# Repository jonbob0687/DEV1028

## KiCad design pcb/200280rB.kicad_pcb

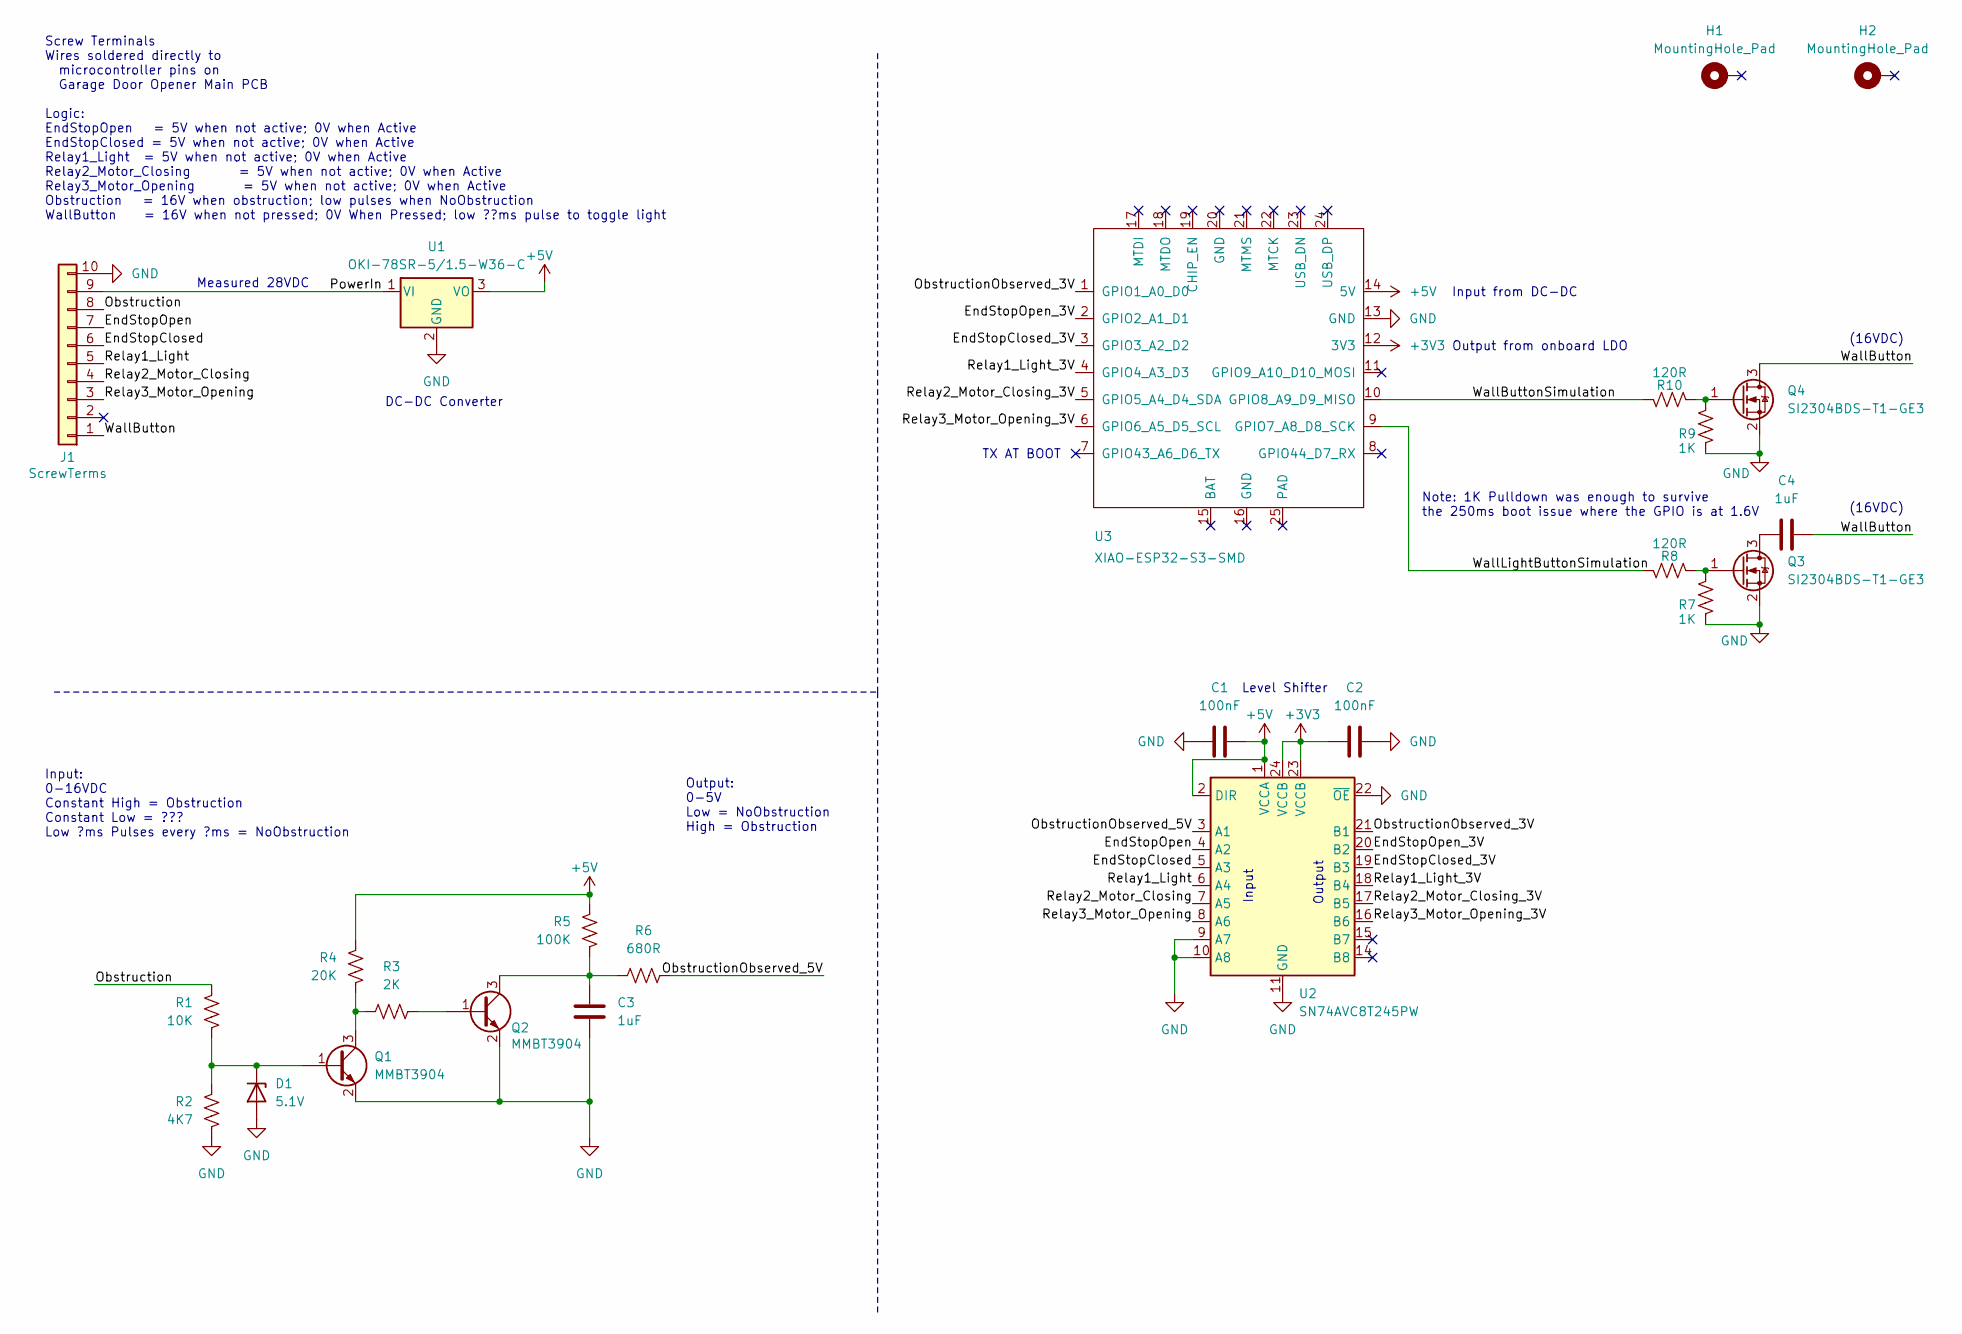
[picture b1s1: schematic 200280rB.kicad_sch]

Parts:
C1, C2: 100nF; C_0603_1608Metric
C3: 1uF; C_0603_1608Metric
C4: 1uF; C_1206_3216Metric_Pad1.33x1.80mm_HandSolder
D1: 5.1V; D_SOD-323_HandSoldering
H1, H2: MountingHole_Pad; MountingHole_3.2mm_M3_Pad
J1: ScrewTerms; phoenix_contact_1984691
Q1, Q2: MMBT3904; SOT-23-3
Q3, Q4: SI2304BDS-T1-GE3; SOT-23
R1: 10K; R_0603_1608Metric
R2: 4K7; R_0603_1608Metric
R3: 2K; R_0603_1608Metric
R4: 20K; R_0603_1608Metric
R5: 100K; R_0603_1608Metric
R6: 680R; R_0603_1608Metric
R7, R9: 1K; R_0603_1608Metric
R8, R10: 120R; R_0603_1608Metric
U1: OKI-78SR-5/1.5-W36-C; TO-220-3_Vertical
U2: SN74AVC8T245PW; TSSOP-24_4.4x7.8mm_P0.65mm
U3: XIAO-ESP32-S3-SMD; XIAO-ESP32S3-SMD

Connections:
+3V3: C2.1, U2.23 (VCCB), U2.24 (VCCB), U3.12 (3V3)
+5V: C1.2, R4.2, R5.2, U1.3 (VO), U2.1 (VCCA), U2.2 (DIR), U3.14 (5V)
/EndStopClosed: J1.6, U2.5 (A3)
/EndStopClosed_3V: U2.19 (B3), U3.3 (GPIO3_A2_D2)
/EndStopOpen: J1.7, U2.4 (A2)
/EndStopOpen_3V: U2.20 (B2), U3.2 (GPIO2_A1_D1)
/Obstruction: J1.8, R1.2
/ObstructionObserved_3V: U2.21 (B1), U3.1 (GPIO1_A0_D0)
/ObstructionObserved_5V: R6.1, U2.3 (A1)
/PowerIn: J1.9, U1.1 (VI)
/Relay1_Light: J1.5, U2.6 (A4)
/Relay1_Light_3V: U2.18 (B4), U3.4 (GPIO4_A3_D3)
/Relay2_Motor_Closing: J1.4, U2.7 (A5)
/Relay2_Motor_Closing_3V: U2.17 (B5), U3.5 (GPIO5_A4_D4_SDA)
/Relay3_Motor_Opening: J1.3, U2.8 (A6)
/Relay3_Motor_Opening_3V: U2.16 (B6), U3.6 (GPIO6_A5_D5_SCL)
/WallButton: C4.2, J1.1, Q4.3 (D)
/WallButtonSimulation: R10.1, U3.10 (GPIO8_A9_D9_MISO)
/WallLightButtonSimulation: R8.1, U3.9 (GPIO7_A8_D8_SCK)
GND: C1.1, C2.2, C3.2, D1.2 (A), J1.10, Q1.2 (E), Q2.2 (E), Q3.2 (S), Q4.2 (S), R2.1, R7.1, R9.1, U1.2 (GND), U2.9 (A7), U2.10 (A8), U2.11 (GND), U2.12 (GND), U2.13 (GND), U2.22 (~OE), U3.13 (GND)
unnamed: D1.1 (K), Q1.1 (B), R1.1, R2.2
unnamed: Q1.3 (C), R3.1, R4.1
unnamed: Q2.1 (B), R3.2
unnamed: C3.1, Q2.3 (C), R5.1, R6.2
unnamed: C4.1, Q3.3 (D)
unnamed: Q3.1 (G), R7.2, R8.2
unnamed: Q4.1 (G), R9.2, R10.2

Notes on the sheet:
(16VDC)
Screw Terminals Wires soldered directly to microcontroller pins on Garage Door Opener Main PCB Logic: EndStopOpen = 5V when not active; 0V when Active EndStopClosed = 5V when not active; 0V when Active Relay1_Light = 5V when not active; 0V when Active Relay2_Motor_Closing = 5V when not active; 0V w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
Output from onboard LDO
Input from DC-DC
Input: 0-16VDC Constant High = Obstruction Constant Low = ??? Low ?ms Pulses every ?ms = NoObstruction
Input
Note: 1K Pulldown was enough to survive the 250ms boot issue where the GPIO is at 1.6V
Output
Measured 28VDC
DC-DC Converter
TX AT BOOT
Level Shifter
Output: 0-5V Low = NoObstruction High = Obstruction

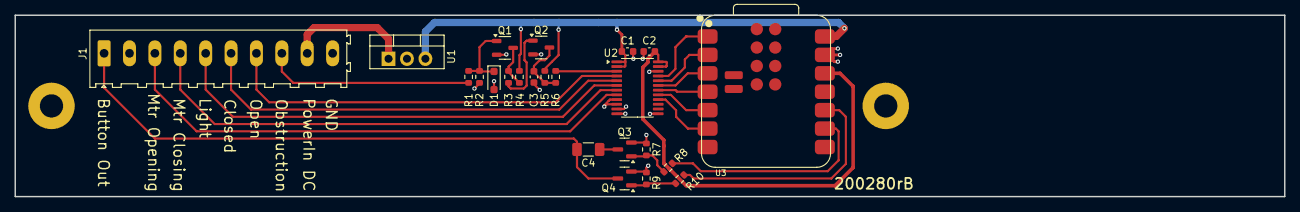
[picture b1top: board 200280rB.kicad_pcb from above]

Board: 2 copper layers, 175.0 x 25.0 mm, 25 parts (0 on the bottom side), 27 nets.

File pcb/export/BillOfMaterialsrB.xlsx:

Reference | Value | Footprint | Qty | DNP | MPN
C1,C2 | 100nF | Capacitor_SMD:C_0603_1608Metric | 2 |  | STASH
C3 | 1uF | Capacitor_SMD:C_0603_1608Metric | 1 |  | CC0603KRX7R9BB105
C4 | 1uF | Capacitor_SMD:C_1206_3216Metric_Pad1.33x1.80mm_HandSolder | 1 |  | HMK316B7105KL-T
D1 | 5.1V | Diode_SMD:D_SOD-323_HandSoldering | 1 |  | DNP
J1 | ScrewTerms | GM_Connector_PhoenixContact:phoenix_contact_1984691 | 1 |  | 1984691
Q1,Q2 | MMBT3904 | Package_TO_SOT_SMD:SOT-23-3 | 2 |  | WORK
Q3,Q4 | SI2304BDS-T1-GE3 | Package_TO_SOT_SMD:SOT-23 | 2 |  | SI2304BDS-T1-GE3
R1 | 10K | Resistor_SMD:R_0603_1608Metric | 1 |  | RC0603FR-0710KL
R2 | 4K7 | Resistor_SMD:R_0603_1608Metric | 1 |  | y
R3 | 2K | Resistor_SMD:R_0603_1608Metric | 1 |  | y
R4 | 20K | Resistor_SMD:R_0603_1608Metric | 1 |  | y
R5 | 100K | Resistor_SMD:R_0603_1608Metric | 1 |  | y
R6 | 680R | Resistor_SMD:R_0603_1608Metric | 1 |  | y
R7,R9 | 1K | Resistor_SMD:R_0603_1608Metric | 2 |  | y
R8,R10 | 120R | Resistor_SMD:R_0603_1608Metric | 2 |  | y
U1 | OKI-78SR-5/1.5-W36-C | Package_TO_SOT_THT:TO-220-3_Vertical | 1 |  | old
U2 | SN74AVC8T245PW | Package_SO:TSSOP-24_4.4x7.8mm_P0.65mm | 1 |  | y
U3 | XIAO-ESP32-S3-SMD | Seeed Studio XIAO Series Library:XIAO-ESP32S3-SMD | 1

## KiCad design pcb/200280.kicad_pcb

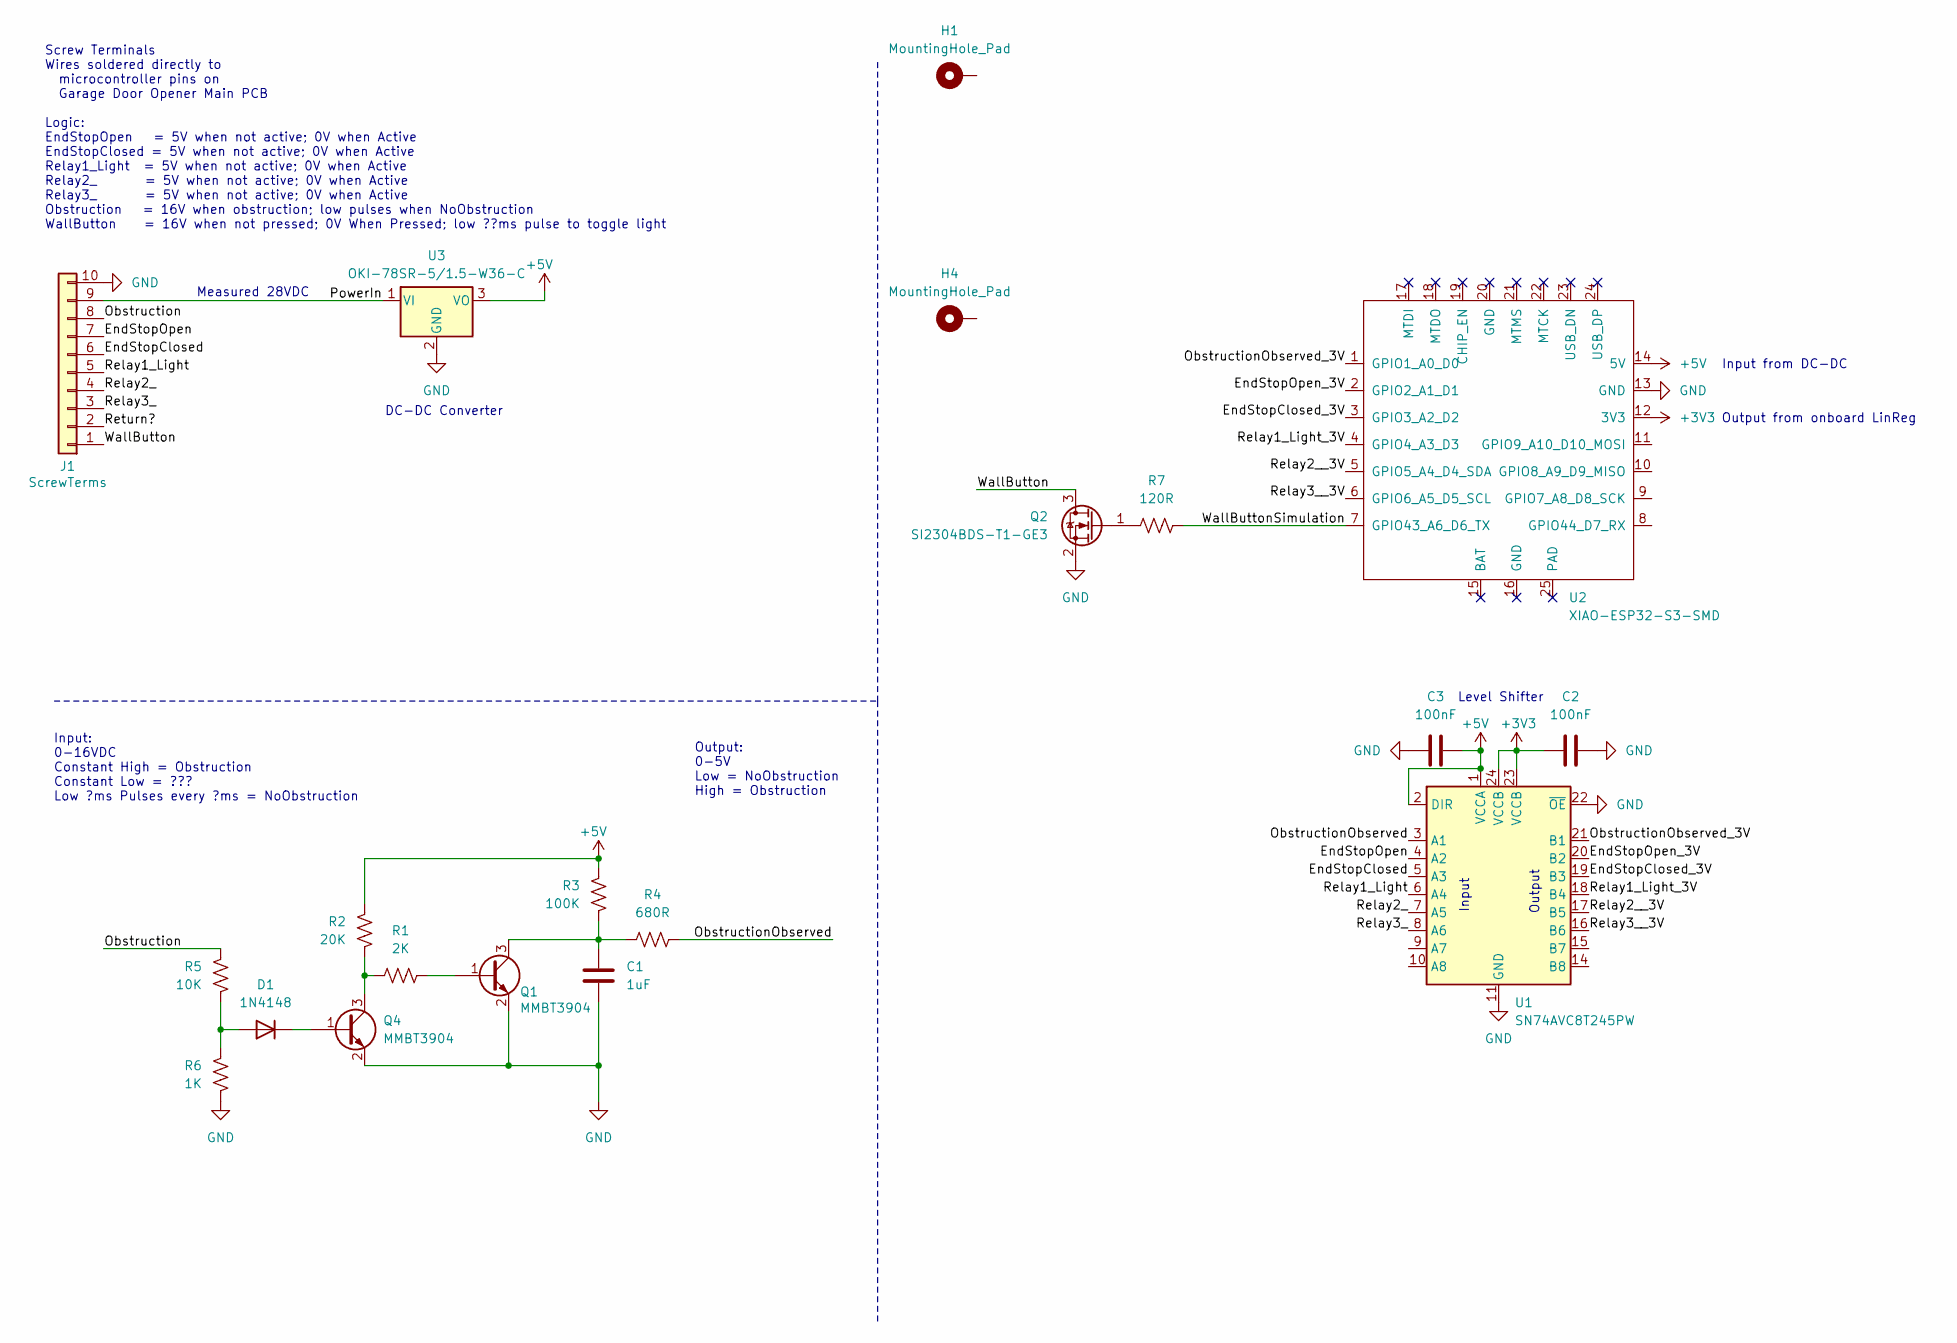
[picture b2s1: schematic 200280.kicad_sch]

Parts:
C1: 1uF; C_0603_1608Metric
C2, C3: 100nF; C_0603_1608Metric
D1: 1N4148; D_SOD-523
H1, H4: MountingHole_Pad; MountingHole_3.2mm_M3_Pad
J1: ScrewTerms; phoenix_contact_1984691
Q1, Q4: MMBT3904; SOT-23-3
Q2: SI2304BDS-T1-GE3; SOT-23
R1: 2K; R_0603_1608Metric
R2: 20K; R_0603_1608Metric
R3: 100K; R_0603_1608Metric
R4: 680R; R_0603_1608Metric
R5: 10K; R_0603_1608Metric
R6: 1K; R_0603_1608Metric
R7: 120R; R_0603_1608Metric
U1: SN74AVC8T245PW; TSSOP-24_4.4x7.8mm_P0.65mm
U2: XIAO-ESP32-S3-SMD; XIAO-ESP32S3-SMD
U3: OKI-78SR-5/1.5-W36-C; TO-220-3_Vertical

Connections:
+3V3: C2.1, U1.23 (VCCB), U1.24 (VCCB), U2.12 (3V3)
+5V: C3.2, R2.2, R3.2, U1.1 (VCCA), U1.2 (DIR), U2.14 (5V), U3.3 (VO)
/EndStopClosed: J1.6, U1.5 (A3)
/EndStopClosed_3V: U1.19 (B3), U2.3 (GPIO3_A2_D2)
/EndStopOpen: J1.7, U1.4 (A2)
/EndStopOpen_3V: U1.20 (B2), U2.2 (GPIO2_A1_D1)
/Obstruction: J1.8, R5.2
/ObstructionObserved: R4.1, U1.3 (A1)
/ObstructionObserved_3V: U1.21 (B1), U2.1 (GPIO1_A0_D0)
/PowerIn: J1.9, U3.1 (VI)
/Relay1_Light: J1.5, U1.6 (A4)
/Relay1_Light_3V: U1.18 (B4), U2.4 (GPIO4_A3_D3)
/Relay2_: J1.4, U1.7 (A5)
/Relay2__3V: U1.17 (B5), U2.5 (GPIO5_A4_D4_SDA)
/Relay3_: J1.3, U1.8 (A6)
/Relay3__3V: U1.16 (B6), U2.6 (GPIO6_A5_D5_SCL)
/Return?: J1.2
/WallButton: J1.1, Q2.3 (D)
/WallButtonSimulation: R7.1, U2.7 (GPIO43_A6_D6_TX)
GND: C1.2, C2.2, C3.1, J1.10, Q1.2 (E), Q2.2 (S), Q4.2 (E), R6.1, U1.11 (GND), U1.12 (GND), U1.13 (GND), U1.22 (~OE), U2.13 (GND), U3.2 (GND)
unnamed: D1.2 (A), R5.1, R6.2
unnamed: D1.1 (K), Q4.1 (B)
unnamed: Q1.1 (B), R1.2
unnamed: C1.1, Q1.3 (C), R3.1, R4.2
unnamed: Q2.1 (G), R7.2
unnamed: Q4.3 (C), R1.1, R2.1

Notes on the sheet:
Screw Terminals Wires soldered directly to microcontroller pins on Garage Door Opener Main PCB Logic: EndStopOpen = 5V when not active; 0V when Active EndStopClosed = 5V when not active; 0V when Active Relay1_Light = 5V when not active; 0V when Active Relay2_ = 5V when not active; 0V when Active Re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
Output from onboard LinReg
Input from DC-DC
Input
Output
Input: 0-16VDC Constant High = Obstruction Constant Low = ??? Low ?ms Pulses every ?ms = NoObstruction
Measured 28VDC
DC-DC Converter
Level Shifter
Output: 0-5V Low = NoObstruction High = Obstruction

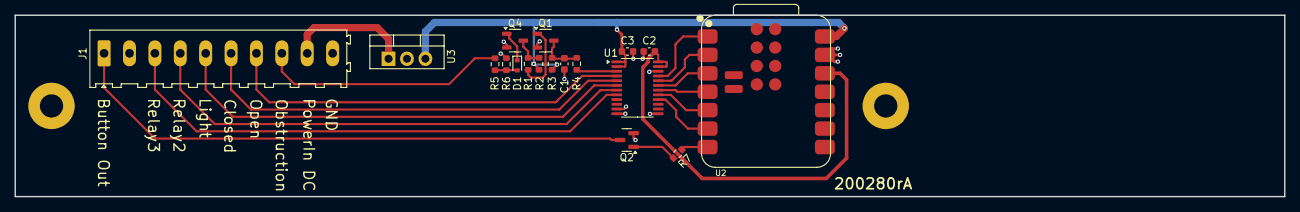
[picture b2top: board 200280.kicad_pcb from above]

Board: 2 copper layers, 175.0 x 25.0 mm, 20 parts (0 on the bottom side), 25 nets.

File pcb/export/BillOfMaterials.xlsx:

Reference | Value | Footprint | Qty | MFR | MPN | Column1
C1 | 1uF | Capacitor_SMD:C_0603_1608Metric | 1 | Murata Electronics North America | GRM188R61A105KA61D
C2,C3 | 100nF | Capacitor_SMD:C_0603_1608Metric | 2 | TDK Corporation | C1608X7R1E104K080AA
D1 | 1N4148 | Diode_SMD:D_SOD-523 | 1 | Diodes Incorporated | 1N4148WT-7 | x
J1 | ScrewTerms | GM_Connector_PhoenixContact:phoenix_contact_1984691 | 1 | Phoenix Contact | 1984691 | x
Q1,Q4 | MMBT3904 | Package_TO_SOT_SMD:SOT-23-3 | 2 | Fairchild Semiconductor | MMBT3904
Q2 | SI2304BDS-T1-GE3 | Package_TO_SOT_SMD:SOT-23 | 1 | VISHAY | SI2304BDS-T1-GE3 | x
R1 | 2K | Resistor_SMD:R_0603_1608Metric | 1
R2 | 20K | Resistor_SMD:R_0603_1608Metric | 1
R3 | 100K | Resistor_SMD:R_0603_1608Metric | 1
R4 | 680R | Resistor_SMD:R_0603_1608Metric | 1
R5 | 10K | Resistor_SMD:R_0603_1608Metric | 1
R6 | 1K | Resistor_SMD:R_0603_1608Metric | 1
R7 | 120R | Resistor_SMD:R_0603_1608Metric | 1
U1 | SN74AVC8T245PW | Package_SO:TSSOP-24_4.4x7.8mm_P0.65mm | 1
U2 | XIAO-ESP32-S3-SMD | Seeed Studio XIAO Series Library:XIAO-ESP32S3-SMD | 1 | Seeed Studio | XIAO-ESP32-S3-SMD
U3 | OKI-78SR-5/1.5-W36-C | Package_TO_SOT_THT:TO-220-3_Vertical | 1 | Murata Power Solutions Inc. | OKI-78SR-5/1.5-W36-C | x

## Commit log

2025-01-17 start
2025-01-17 basic design
2025-01-20 final PCB design as purchased rev A
2025-02-19 add notes
2025-02-19 add diode stuff
2025-03-09 with diode drops
2025-03-09 as purchased revision B
